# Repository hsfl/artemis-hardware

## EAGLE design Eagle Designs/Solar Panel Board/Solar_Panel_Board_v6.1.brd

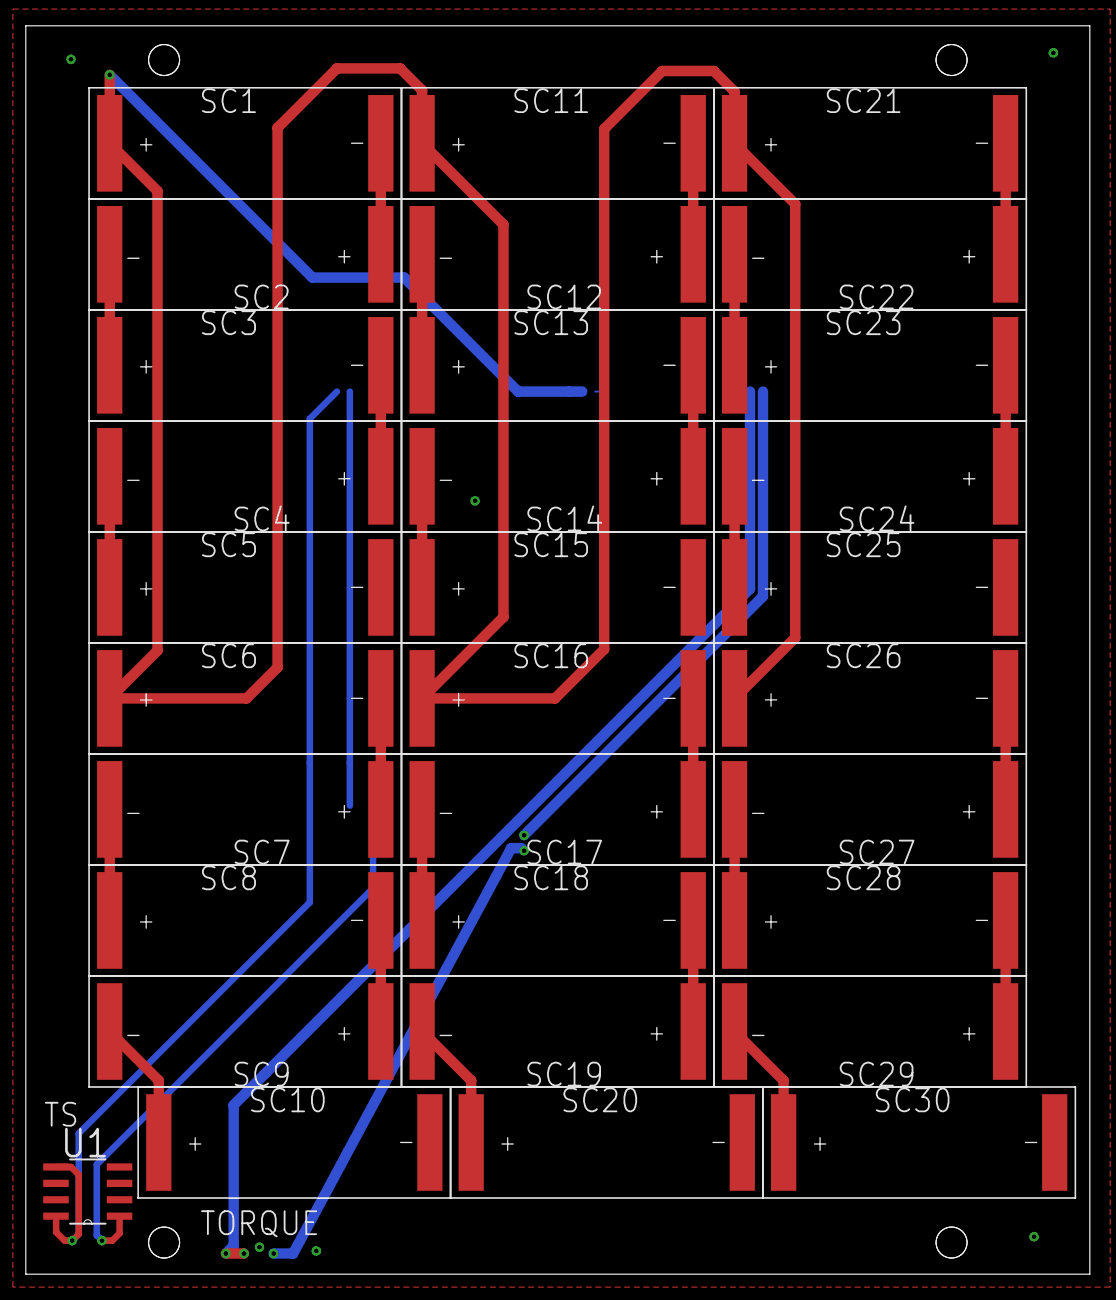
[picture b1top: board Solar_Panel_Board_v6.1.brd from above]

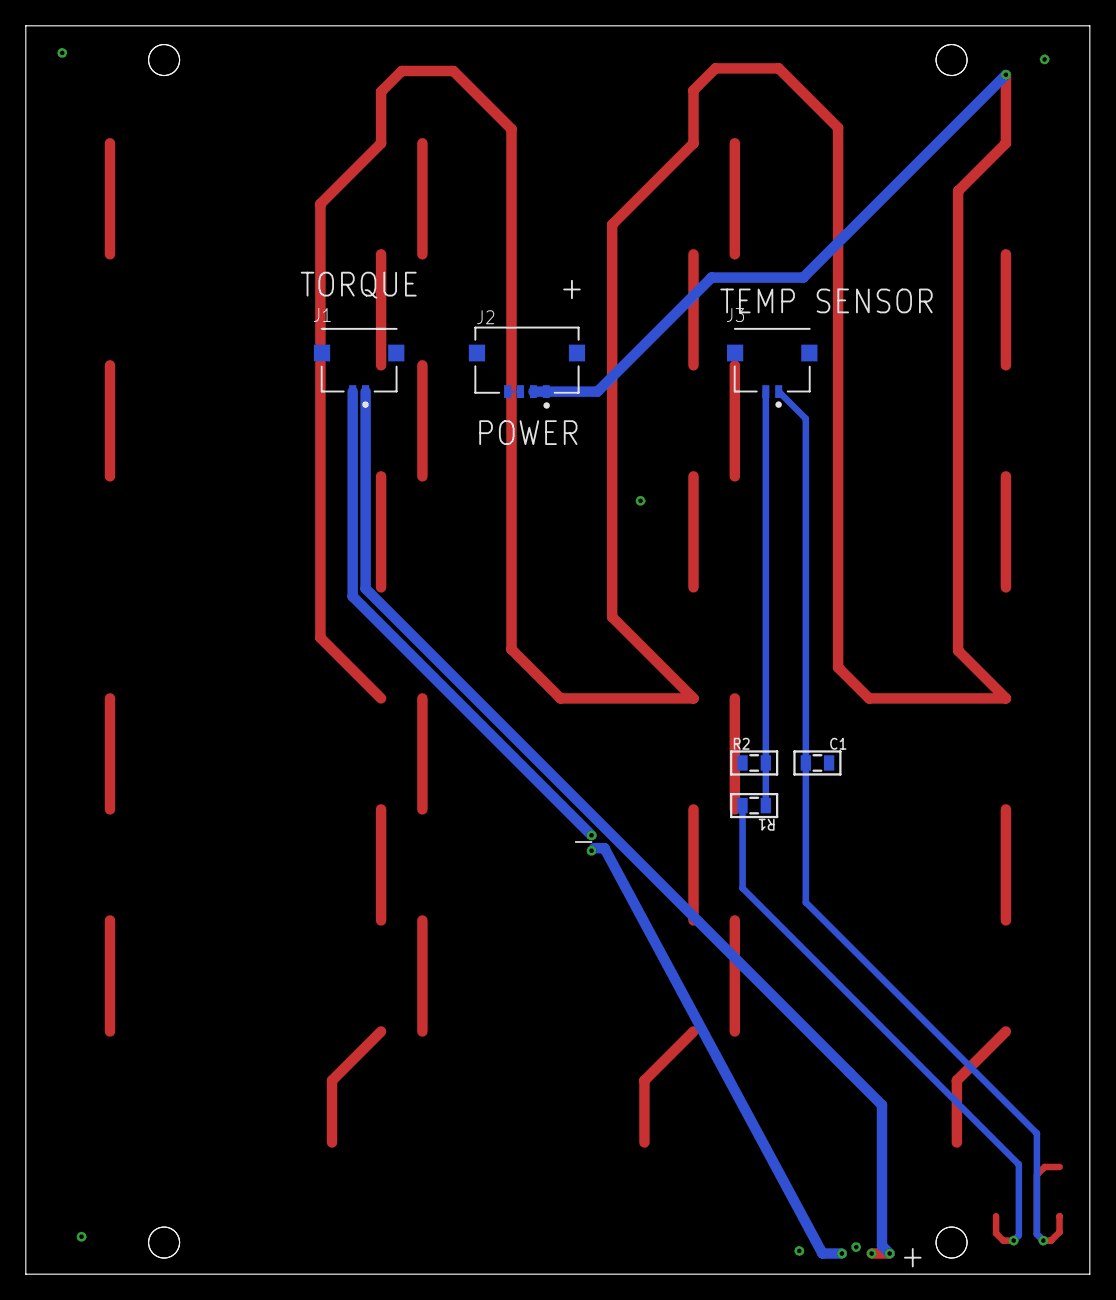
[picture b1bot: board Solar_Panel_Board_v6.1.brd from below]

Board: 4 copper layers, 82.4 x 96.7 mm, 37 parts (6 on the bottom side), 30 nets.

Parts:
C1: 0.1uF; 0805
J1, J3: MOLEX_503763-0291MOLEX_503763-0291_0_0; MOLEX_503763-0291_0
J2: MOLEX_503763-0491MOLEX_503763-0491_0_0; MOLEX_503763-0491_0
R1: 45.3k; 0805
R2: 10k; 0805
SC1, SC2, SC3, SC4, SC5, SC6, SC7, SC8, SC9, SC10, SC11, SC12, SC13, SC14, SC15, SC16, SC17, SC18, SC19, SC20, SC21, SC22, SC23, SC24, SC25, SC26, SC27, SC28, SC29, SC30: KXOB25-05X3F
U1: TMP36GSZ; SOIC127P600X175-8N

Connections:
GND: C1.2, J1.3, J1.4, J2.3, J2.4, J2.5, J2.6, J3.3, J3.4, R2.1, SC5.-, SC10.-, SC15.-, SC20.-, SC25.-, SC30.-, U1.4
unnamed: J1.1, J1.2
unnamed: SC7.-, SC8.+
unnamed: SC4.-, SC5.+
unnamed: SC3.-, SC4.+
unnamed: SC2.-, SC3.+
unnamed: SC1.-, SC2.+
unnamed: SC8.-, SC9.+
unnamed: SC16.-, SC17.+
unnamed: SC14.-, SC15.+
unnamed: SC13.-, SC14.+
unnamed: SC9.-, SC10.+
unnamed: R1.2, U1.1
unnamed: SC11.-, SC12.+
unnamed: SC23.-, SC24.+
unnamed: SC22.-, SC23.+
unnamed: SC21.-, SC22.+
unnamed: SC6.-, SC7.+
unnamed: SC17.-, SC18.+
unnamed: SC19.-, SC20.+
unnamed: SC12.-, SC13.+
unnamed: SC28.-, SC29.+
unnamed: SC29.-, SC30.+
unnamed: SC26.-, SC27.+
unnamed: SC24.-, SC25.+
unnamed: SC18.-, SC19.+
unnamed: SC27.-, SC28.+
VCC: J2.1, J2.2, SC1.+, SC6.+, SC11.+, SC16.+, SC21.+, SC26.+
VOUT: J3.2, R1.1, R2.2
VS+: C1.1, J3.1, U1.5, U1.8

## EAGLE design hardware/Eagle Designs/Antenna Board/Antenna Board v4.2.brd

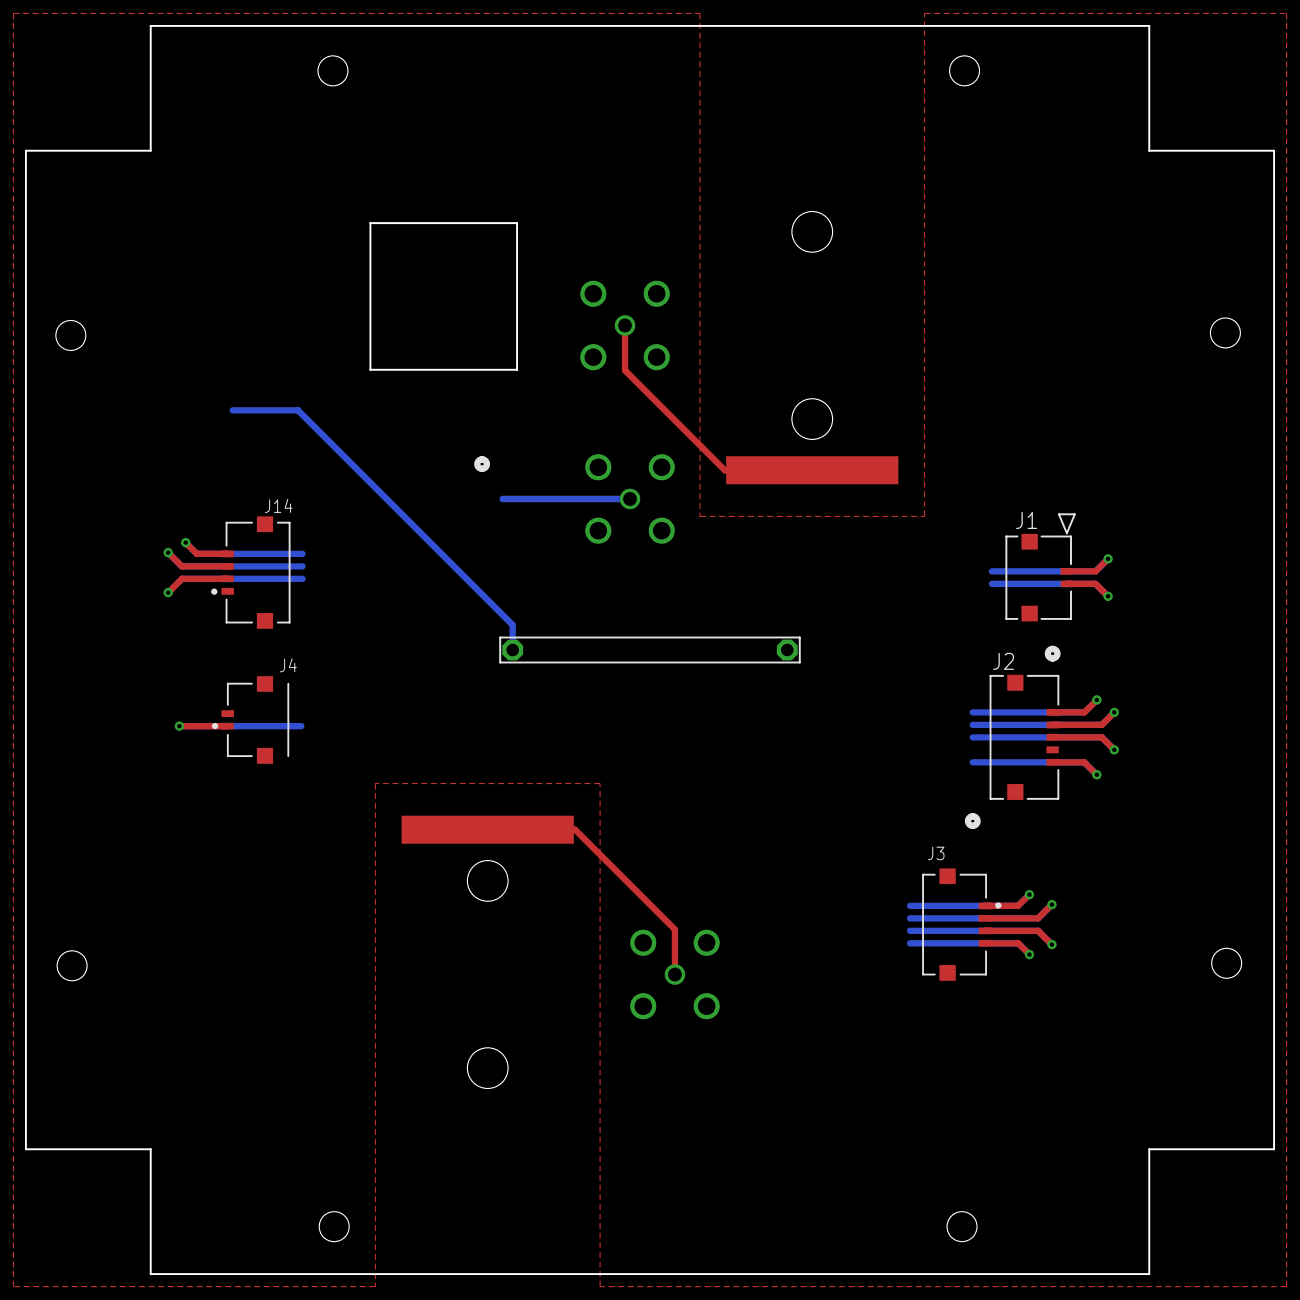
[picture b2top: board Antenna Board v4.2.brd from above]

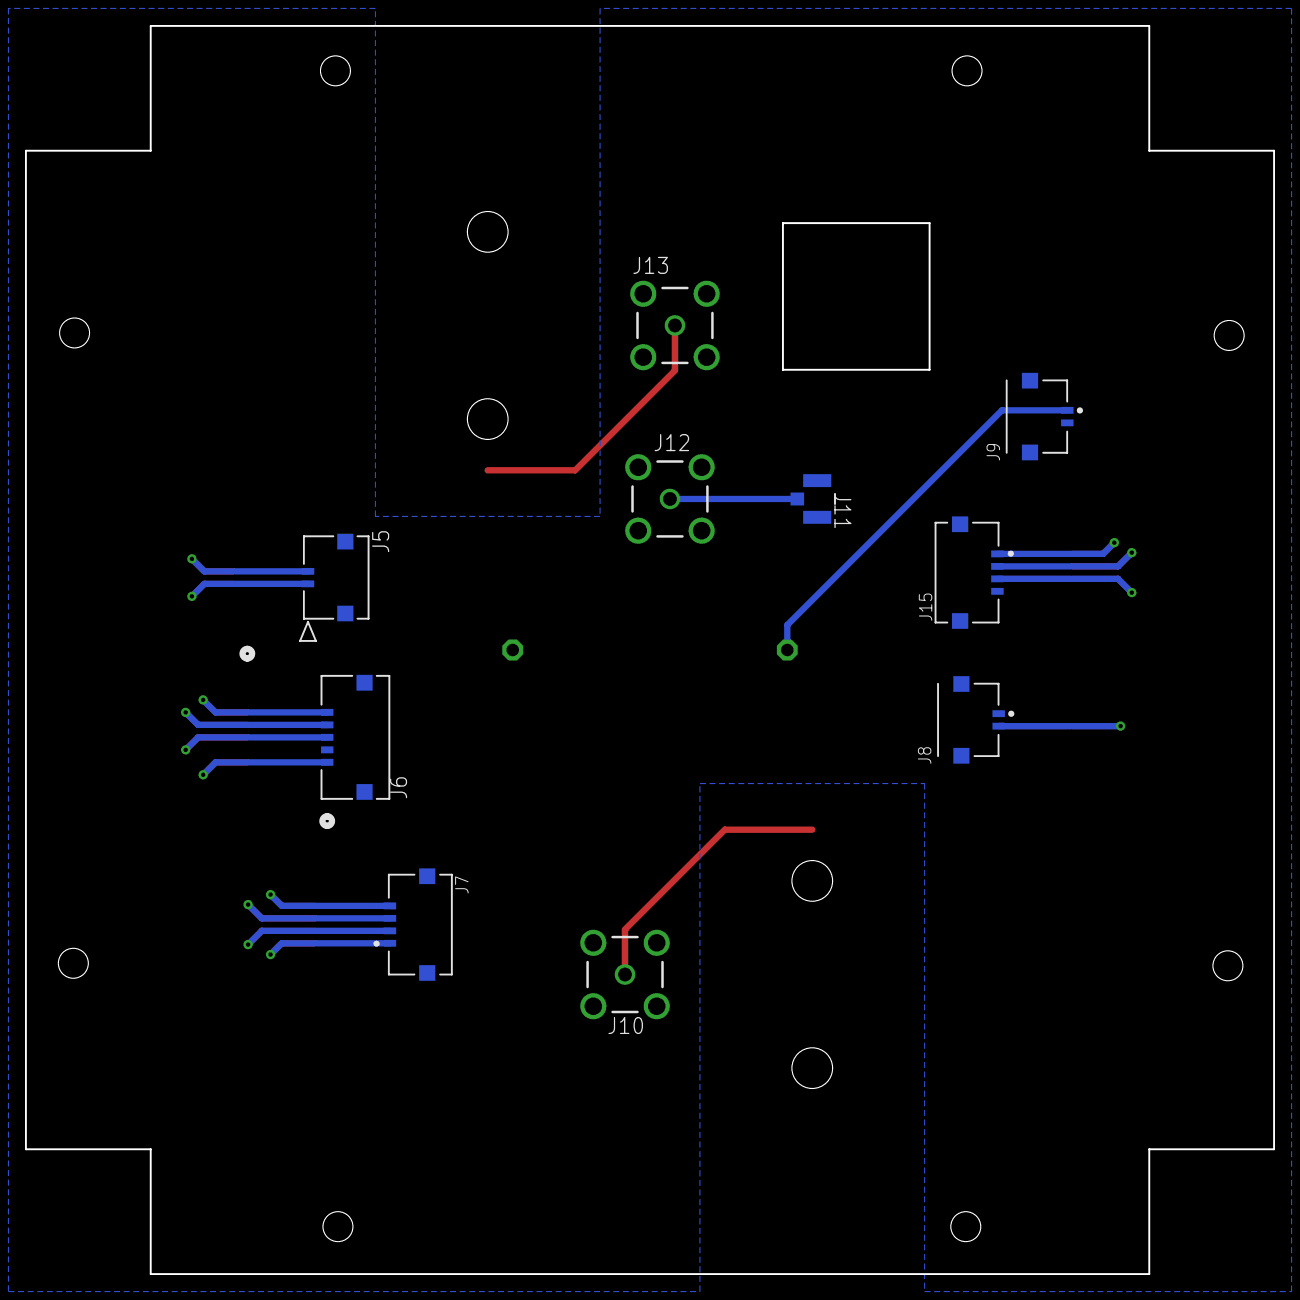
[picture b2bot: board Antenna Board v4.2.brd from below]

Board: 2 copper layers, 100.0 x 100.0 mm, 18 parts (10 on the bottom side), 19 nets.

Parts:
J1, J5: 5037630291; CON_5037630291
J2, J6: 503763-0591; CONN_5037630591_MOL
J3, J7, J14, J15: MOLEX_503763-0491MOLEX_503763-0491_0_0; MOLEX_503763-0491_0
J4, J8, J9: MOLEX_503763-0291MOLEX_503763-0291_0_0; MOLEX_503763-0291_0
J10, J12, J13: MCX-J-P-X-ST-TH1; SAMTEC_MCX-J-P-X-ST-TH1
J11: U.FL-R-SMT-1(01); CONN_-SMT-1(01)
U$1, U$2: ANTENNA_PAD+HOLES
U$3: BURNWIRE

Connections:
5V: J14.2, J15.3
ANTENNA1: J10.1, U$1.1
ANTENNA2: J13.1, U$2.1
D+: J14.3, J15.2
D-: J14.4, J15.1
GND: J1.3, J1.4, J2.4, J2.6, J2.7, J3.5, J3.6, J4.2, J4.3, J4.4, J5.3, J5.4, J6.2, J6.6, J6.7, J7.5, J7.6, J8.1, J8.3, J8.4, J9.2, J9.3, J9.4, J10.S1, J10.S2, J10.S3, J10.S4, J11.1, J11.2, J12.S1, J12.S2, J12.S3, J12.S4, J13.S1, J13.S2, J13.S3, J13.S4, J14.1, J14.5, J14.6, J15.4, J15.5, J15.6, U$3.2
ORION-SPACE: J11.3, J12.1
RBF1: J1.1, J5.2
RBF2: J1.2, J5.1
RESET: J2.1, J6.5
RX+: J3.1, J7.4
RX-: J3.2, J7.3
TCK: J2.2, J6.4
TMS: J2.3, J6.3
TX+: J3.3, J7.2
TX-: J3.4, J7.1
VCC_BATT: J4.1, J8.2
VCC_BURN: J9.1, U$3.1
VRTREF: J2.5, J6.1

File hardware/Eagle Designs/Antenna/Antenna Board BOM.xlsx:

Part | Value | Device | Package | Description
J1, J5 | 503763-0591 | 503763-0591 | CONN_5037630591_MOL
J2, J3, J6, J7 | 503763-0491 | MOLEX_503763-0491MOLEX_503763-0491_0_0 | MOLEX_503763-0491_0 | Wire-To-Board Connector, Pico-Lock 503763 Series, Surface Mount, Header, 4 Cont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
J4, J8, J9 | 503763-0291 | MOLEX_503763-0291MOLEX_503763-0291_0_0 | MOLEX_503763-0291_0 | 2 Positions Header Connector 0.039 (1.00mm) Surface Mount, Right Angle Gold"
J10 | U.FL-R-SMT-1(01) | U.FL-R-SMT-1(01) | CONN_-SMT-1(01)
U$2 | ANTENNA_PAD | ANTENNA_PAD | ANTENNA_PAD
U$3 | BURNWIRE | BURNWIRE | BURNWIRE

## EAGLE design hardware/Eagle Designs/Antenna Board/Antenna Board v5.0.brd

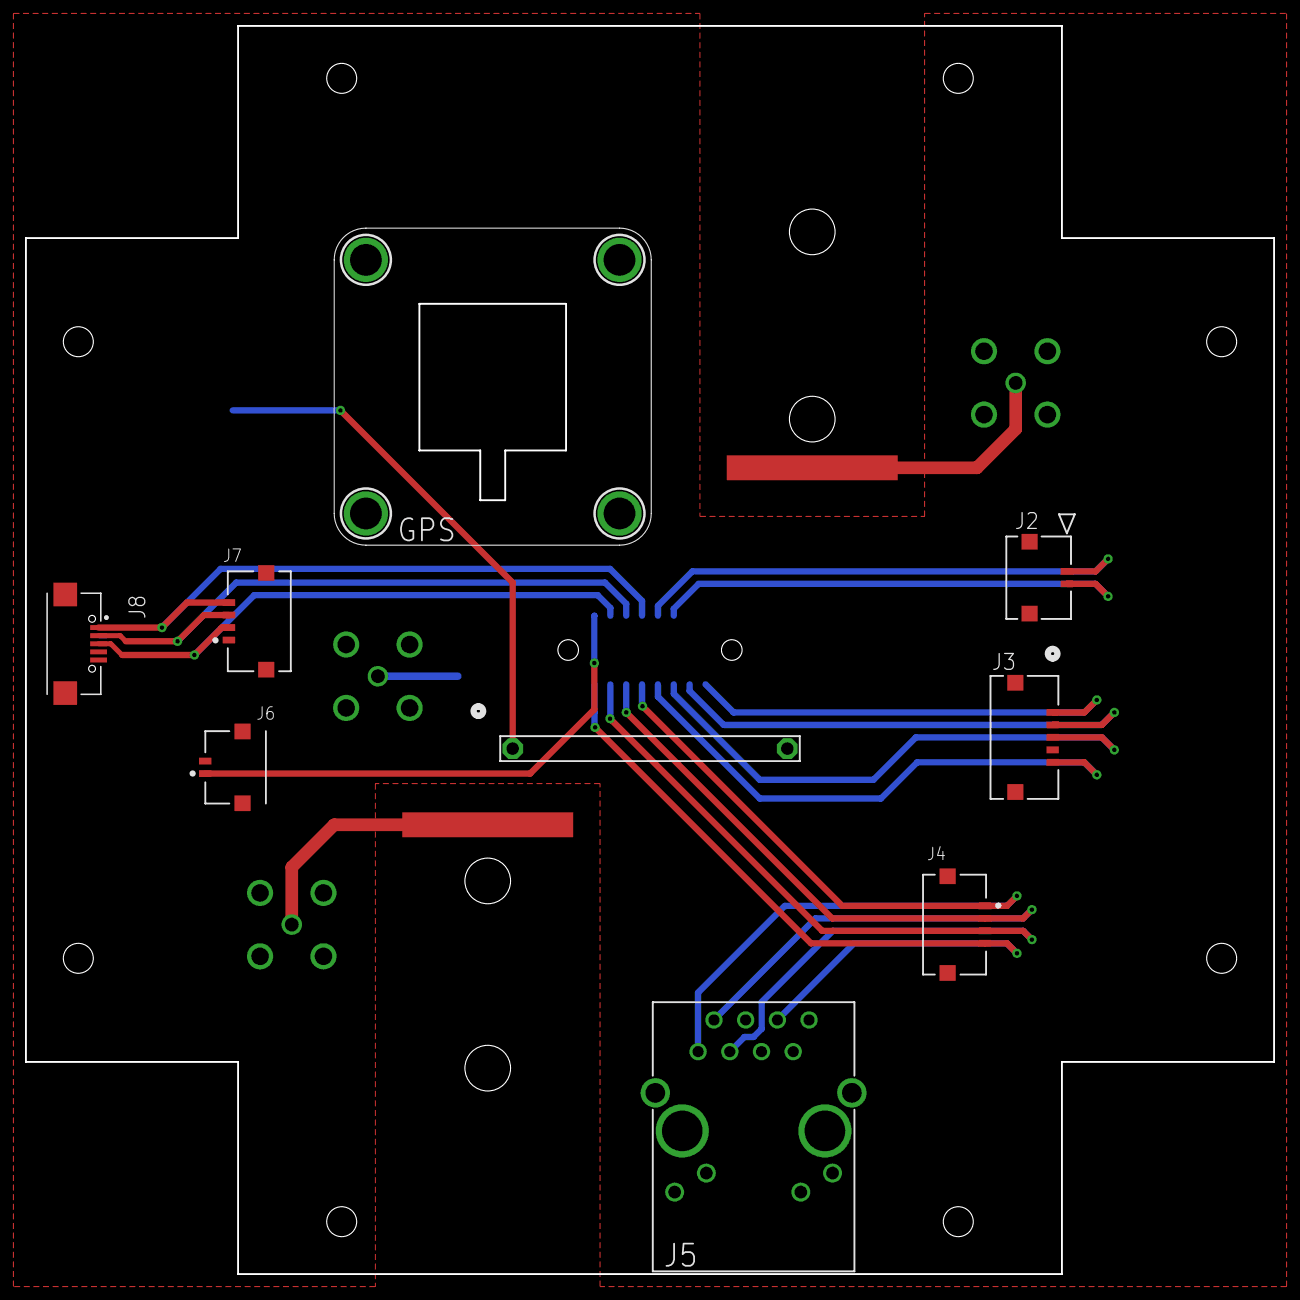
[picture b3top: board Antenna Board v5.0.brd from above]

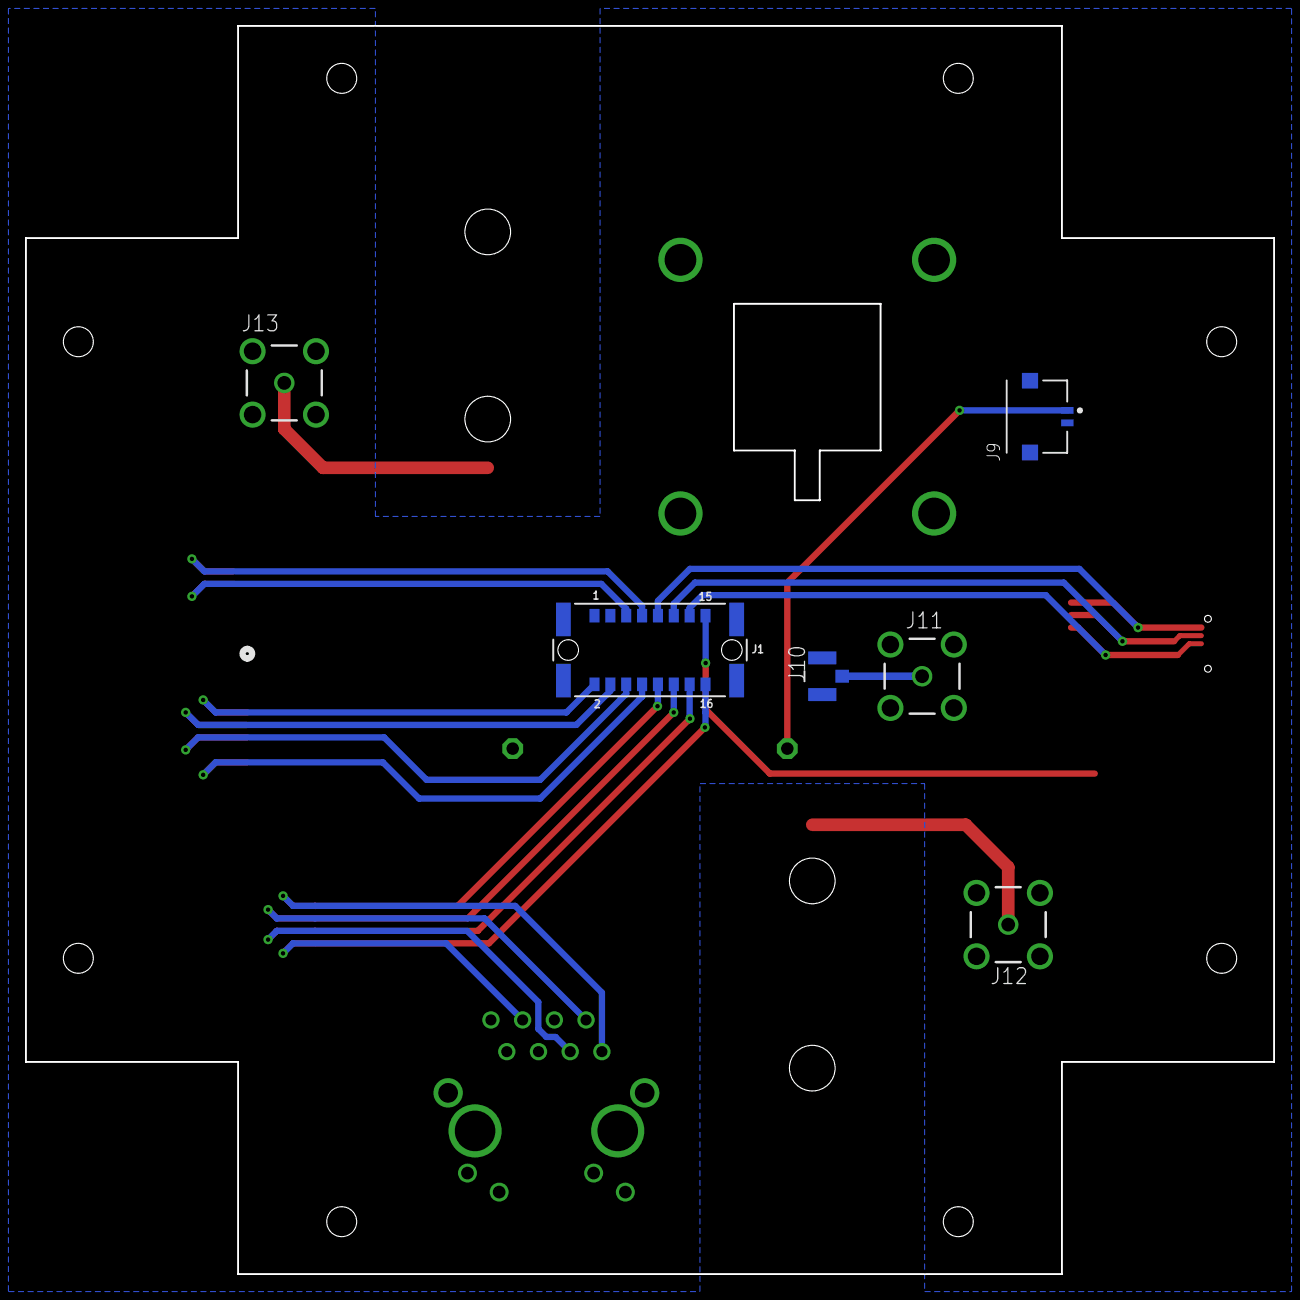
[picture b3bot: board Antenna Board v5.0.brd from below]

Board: 2 copper layers, 100.0 x 100.0 mm, 17 parts (6 on the bottom side), 19 nets.

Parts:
GPS: PA1010D
J1: M55-6001642R; CONN_M55-6001642R_HRW
J2: 5037630291; CON_5037630291
J3: 503763-0591; CONN_5037630591_MOL
J4, J7: MOLEX_503763-0491MOLEX_503763-0491_0_0; MOLEX_503763-0491_0
J5: ARJM11C7-104-AB-EW2; CONN_EW_ABR
J6, J9: MOLEX_503763-0291MOLEX_503763-0291_0_0; MOLEX_503763-0291_0
J8: UJ2-MIBH-G-SMT-TR; CUI_UJ2-MIBH-G-SMT-TR
J10: U.FL-R-SMT-1(01); CONN_-SMT-1(01)
J11, J12, J13: MCX-J-P-X-ST-TH1; SAMTEC_MCX-J-P-X-ST-TH1
U$1, U$2: ANTENNA_PAD
U$3: BURNWIRE

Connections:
5V: J1.9, J7.4, J8.1
ANTENNA1: J12.1, U$2.1
ANTENNA2: J13.1, U$1.1
D+: J1.13, J7.2, J8.3
D-: J1.11, J7.3, J8.2
GND: J1.1, J1.3, J1.19, J1.20, J1.21, J1.22, J2.3, J2.4, J3.4, J3.6, J3.7, J4.5, J4.6, J6.2, J6.3, J6.4, J7.1, J7.5, J7.6, J8.5, J8.S1, J8.S2, J9.2, J9.3, J9.4, J10.1, J10.2, J11.S1, J11.S2, J11.S3, J11.S4, J12.S1, J12.S2, J12.S3, J12.S4, J13.S1, J13.S2, J13.S3, J13.S4, U$3.2
ORION-SPACE: J10.3, J11.1
RBF1: J1.7, J2.1
RBF2: J1.5, J2.2
RESET: J1.2, J3.1
RX+: J1.14, J4.3, J5.3
RX-: J1.16, J4.4, J5.6
TCK: J1.4, J3.2
TMS: J1.6, J3.3
TX+: J1.10, J4.1, J5.1
TX-: J1.12, J4.2, J5.2
VCC_BATT: J1.15, J6.1
VCC_BURN: J9.1, U$3.1
VRTREF: J1.8, J3.5

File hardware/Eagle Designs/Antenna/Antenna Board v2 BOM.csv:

"Part";"Value";"Device";"Package";"Description";"AUTOMOTIVE";"BUILT_BY";"CENTROID_NOT_SPECIFIED";"CONN_GENDER";"CONN_ORIENTATION";"CONTACT_MATERIAL";"COPYRIGHT";"CURRENT_RATING";"DATASHEET";"DEVICE_CLASS_L1";"DEVICE_CLASS_L2";"DEVICE_CLASS_L3";"DIGIKEY_DESCRIPTION";"DIGIKEY_PART_NUMBER";"FOOTPRINT_URL";"FOOTPRINT_VARIANT_NAME_0";"HEIGHT";"LEAD_FREE";"MANUFACTURER_PART_NUMBER";"MF";"MFG_PACKAGE_IDENT";"MFG_PACKAGE_IDENT_DATE";"MFG_PACKAGE_IDENT_REV";"MOUSER_PART_NUMBER";"MPN";"NUMBER_OF_CONTACTS";"NUMBER_OF_ROWS";"PACKAGE";"PITCH";"PREFIX";"ROHS";"SOURCELIBRARY";"TEMPERATURE_RANGE_HIGH";"TEMPERATURE_RANGE_LOW";"VENDOR";"VERIFICATION_VERSION";"VOLTAGE_RATING";
"J1";"503763-0591";"503763-0591";"CONN_5037630591_MOL";"";"";"EMA_Cory";"";"";"";"";"Copyright (C) 2018 Accelerated Designs. All rights reserved";"";"https://www.molex.com/pdm_docs/sd/5037630591_sd.pdf";"";"";"";"";"";"";"";"";"";"503763-0591";"";"";"";"";"";"";"";"";"";"";"";"";"Add_to_database_2020-12-14";"";"";"Molex Connector Corporation";"";"";
"J2";"MOLEX_503763-0491MOLEX_503763-0491_0_0";"MOLEX_503763-0491MOLEX_503763-0491_0_0";"MOLEX_503763-0491_0";"Wire-To-Board Connector, Pico-Lock 503763 Series, Surface Mount, Header, 4 Contacts, 1 mm";"No";"";"No";"Male";"Right Angle";"Gold,Nickel";"";"1.5A";"https://www.molex.com/webdocs/datasheets/pdf/en-us/503763049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";"Connectors";"Headers and Wire Housings";"unset";"CONN HEADER 1MM R/A 4CKT";"WM10655CT-ND";"https://www.molex.com/pdm_docs/sd/5037630491_sd.pdf";"Recommended_Land_Pattern";"1.7mm";"Yes";"";"Molex";"503763-0491";"0";"0";"538-503763-0491";"503763-0491";"4";"1";"HDR4";"1mm";"J";"Yes";"";"+105°C";"-40°C";"";"0.0.0.1";"150V";
"J3";"MOLEX_503763-0491MOLEX_503763-0491_0_0";"MOLEX_503763-0491MOLEX_503763-0491_0_0";"MOLEX_503763-0491_0";"Wire-To-Board Connector, Pico-Lock 503763 Series, Surface Mount, Header, 4 Contacts, 1 mm";"No";"";"No";"Male";"Right Angle";"Gold,Nickel";"";"1.5A";"https://www.molex.com/webdocs/datasheets/pdf/en-us/503763049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";"Connectors";"Headers and Wire Housings";"unset";"CONN HEADER 1MM R/A 4CKT";"WM10655CT-ND";"https://www.molex.com/pdm_docs/sd/5037630491_sd.pdf";"Recommended_Land_Pattern";"1.7mm";"Yes";"";"Molex";"503763-0491";"0";"0";"538-503763-0491";"503763-0491";"4";"1";"HDR4";"1mm";"J";"Yes";"";"+105°C";"-40°C";"";"0.0.0.1";"150V";
"J4";"MOLEX_503763-0291MOLEX_503763-0291_0_0";"MOLEX_503763-0291MOLEX_503763-0291_0_0";"MOLEX_503763-0291_0";"2 Positions Header Connector 0.039" (1.00mm) Surface Mount, Right Angle Gold";"";"";"No";"";"";"";"";"";"http://www.molex.com/pdm_docs/sd/5037630291_sd.pdf";"";"";"";"CONN HEADER 1MM R/A 2CKT";"WM10654CT-ND";"";"";"";"yes";"";"Molex";"";"";"";"538-503763-0291";"503763-0291";"";"";"HDR02";"";"J";"yes";"";"+105°C";"-40°C";"";"";"";
"J5";"503763-0591";"503763-0591";"CONN_5037630591_MOL";"";"";"EMA_Cory";"";"";"";"";"Copyright (C) 2018 Accelerated Designs. All rights reserved";"";"https://www.molex.com/pdm_docs/sd/5037630591_sd.pdf";"";"";"";"";"";"";"";"";"";"503763-0591";"";"";"";"";"";"";"";"";"";"";"";"";"Add_to_database_2020-12-14";"";"";"Molex Connector Corporation";"";"";
"J6";"MOLEX_503763-0491MOLEX_503763-0491_0_0";"MOLEX_503763-0491MOLEX_503763-0491_0_0";"MOLEX_503763-0491_0";"Wire-To-Board Connector, Pico-Lock 503763 Series, Surface Mount, Header, 4 Contacts, 1 mm";"No";"";"No";"Male";"Right Angle";"Gold,Nickel";"";"1.5A";"https://www.molex.com/webdocs/datasheets/pdf/en-us/503763049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";"Connectors";"Headers and Wire Housings";"unset";"CONN HEADER 1MM R/A 4CKT";"WM10655CT-ND";"https://www.molex.com/pdm_docs/sd/5037630491_sd.pdf";"Recommended_Land_Pattern";"1.7mm";"Yes";"";"Molex";"503763-0491";"0";"0";"538-503763-0491";"503763-0491";"4";"1";"HDR4";"1mm";"J";"Yes";"";"+105°C";"-40°C";"";"0.0.0.1";"150V";
"J7";"MOLEX_503763-0491MOLEX_503763-0491_0_0";"MOLEX_503763-0491MOLEX_503763-0491_0_0";"MOLEX_503763-0491_0";"Wire-To-Board Connector, Pico-Lock 503763 Series, Surface Mount, Header, 4 Contacts, 1 mm";"No";"";"No";"Male";"Right Angle";"Gold,Nickel";"";"1.5A";"https://www.molex.com/webdocs/datasheets/pdf/en-us/503763049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";"Connectors";"Headers and Wire Housings";"unset";"CONN HEADER 1MM R/A 4CKT";"WM10655CT-ND";"https://www.molex.com/pdm_docs/sd/5037630491_sd.pdf";"Recommended_Land_Pattern";"1.7mm";"Yes";"";"Molex";"503763-0491";"0";"0";"538-503763-0491";"503763-0491";"4";"1";"HDR4";"1mm";"J";"Yes";"";"+105°C";"-40°C";"";"0.0.0.1";"150V";
"J8";"MOLEX_503763-0291MOLEX_503763-0291_0_0";"MOLEX_503763-0291MOLEX_503763-0291_0_0";"MOLEX_503763-0291_0";"2 Positions Header Connector 0.039" (1.00mm) Surface Mount, Right Angle Gold";"";"";"No";"";"";"";"";"";"http://www.molex.com/pdm_docs/sd/5037630291_sd.pdf";"";"";"";"CONN HEADER 1MM R/A 2CKT";"WM10654CT-ND";"";"";"";"yes";"";"Molex";"";"";"";"538-503763-0291";"503763-0291";"";"";"HDR02";"";"J";"yes";"";"+105°C";"-40°C";"";"";"";
"J9";"MOLEX_503763-0291MOLEX_503763-0291_0_0";"MOLEX_503763-0291MOLEX_503763-0291_0_0";"MOLEX_503763-0291_0";"2 Positions Header Connector 0.039" (1.00mm) Surface Mount, Right Angle Gold";"";"";"No";"";"";"";"";"";"http://www.molex.com/pdm_docs/sd/5037630291_sd.pdf";"";"";"";"CONN HEADER 1MM R/A 2CKT";"WM10654CT-ND";"";"";"";"yes";"";"Molex";"";"";"";"538-503763-0291";"503763-0291";"";"";"HDR02";"";"J";"yes";"";"+105°C";"-40°C";"";"";"";
"J10";"U.FL-R-SMT-1(01)";"U.FL-R-SMT-1(01)";"CONN_-SMT-1(01)";"";"";"EMA_Matt";"";"";"";"";"Copyright (C) 2018 Accelerated Designs. All rights reserved";"";"";"";"";"";"";"";"";"";"";"";"U.FL-R-SMT-1(01)";"";"";"";"";"";"";"";"";"";"";"";"";"Hirose_12_20_2019";"";"";"Hirose";"";"";
"J11";"U.FL-R-SMT-1(01)";"U.FL-R-SMT-1(01)";"CONN_-SMT-1(01)";"";"";"EMA_Matt";"";"";"";"";"Copyright (C) 2018 Accelerated Designs. All rights reserved";"";"";"";"";"";"";"";"";"";"";"";"U.FL-R-SMT-1(01)";"";"";"";"";"";"";"";"";"";"";"";"";"Hirose_12_20_2019";"";"";"Hirose";"";"";
"J12";"U.FL-R-SMT-1(01)";"U.FL-R-SMT-1(01)";"CONN_-SMT-1(01)";"";"";"EMA_Matt";"";"";"";"";"Copyright (C) 2018 Accelerated Designs. All rights reserved";"";"";"";"";"";"";"";"";"";"";"";"U.FL-R-SMT-1(01)";"";"";"";"";"";"";"";"";"";"";"";"";"Hirose_12_20_2019";"";"";"Hirose";"";"";
"U$2";"ANTENNA_PAD";"ANTENNA_PAD";"ANTENNA_PAD";"";"";"";"";"";"";"";"";"";"";"";"";"";"";"";"";"";"";"";"";"";"";"";"";"";"";"";"";"";"";"";"";"";"";"";"";"";"";
"U$3";"BURNWIRE";"BURNWIRE";"BURNWIRE";"";"";"";"";"";"";"";"";"";"";"";"";"";"";"";"";"";"";"";"";"";"";"";"";"";"";"";"";"";"";"";"";"";"";"";"";"";"";

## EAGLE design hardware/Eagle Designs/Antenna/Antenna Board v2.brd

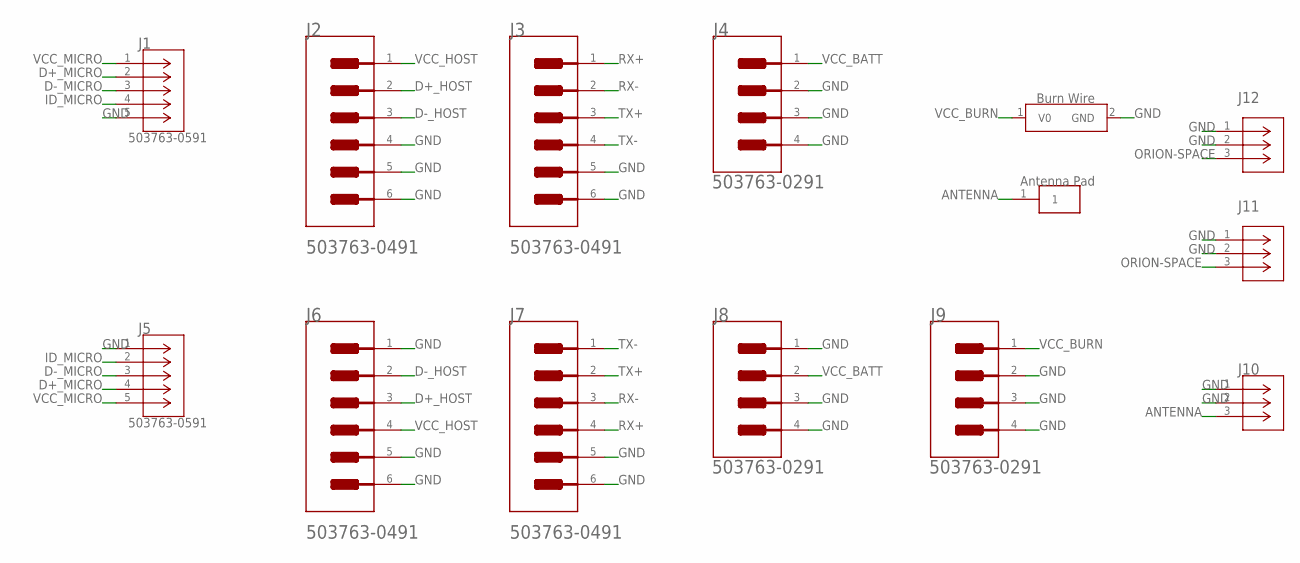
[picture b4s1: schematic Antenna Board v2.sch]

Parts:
J1, J5: 503763-0591; CONN_5037630591_MOL
J2, J3, J6, J7: MOLEX_503763-0491MOLEX_503763-0491_0_0; MOLEX_503763-0491_0
J4, J8, J9: MOLEX_503763-0291MOLEX_503763-0291_0_0; MOLEX_503763-0291_0
J10, J11, J12: U.FL-R-SMT-1(01); CONN_-SMT-1(01)
U$2: ANTENNA_PAD
U$3: BURNWIRE

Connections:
ANTENNA: J10.3, U$2.1
D+_HOST: J2.2, J6.3
D+_MICRO: J1.2, J5.4
D-_HOST: J2.3, J6.2
D-_MICRO: J1.3, J5.3
GND: J1.5, J1.6, J1.7, J2.4, J2.5 (MNT_1), J2.6 (MNT_2), J3.5 (MNT_1), J3.6 (MNT_2), J4.2, J4.3 (MNT_1), J4.4 (MNT_2), J5.1, J5.6, J5.7, J6.1, J6.5 (MNT_1), J6.6 (MNT_2), J7.5 (MNT_1), J7.6 (MNT_2), J8.1, J8.3 (MNT_1), J8.4 (MNT_2), J9.2, J9.3 (MNT_1), J9.4 (MNT_2), J10.1, J10.2, J11.1, J11.2, J12.1, J12.2, U$3.2 (GND)
ID_MICRO: J1.4, J5.2
ORION-SPACE: J11.3, J12.3
RX+: J3.1, J7.4
RX-: J3.2, J7.3
TX+: J3.3, J7.2
TX-: J3.4, J7.1
VCC_BATT: J4.1, J8.2
VCC_BURN: J9.1, U$3.1 (V0)
VCC_HOST: J2.1, J6.4
VCC_MICRO: J1.1, J5.5

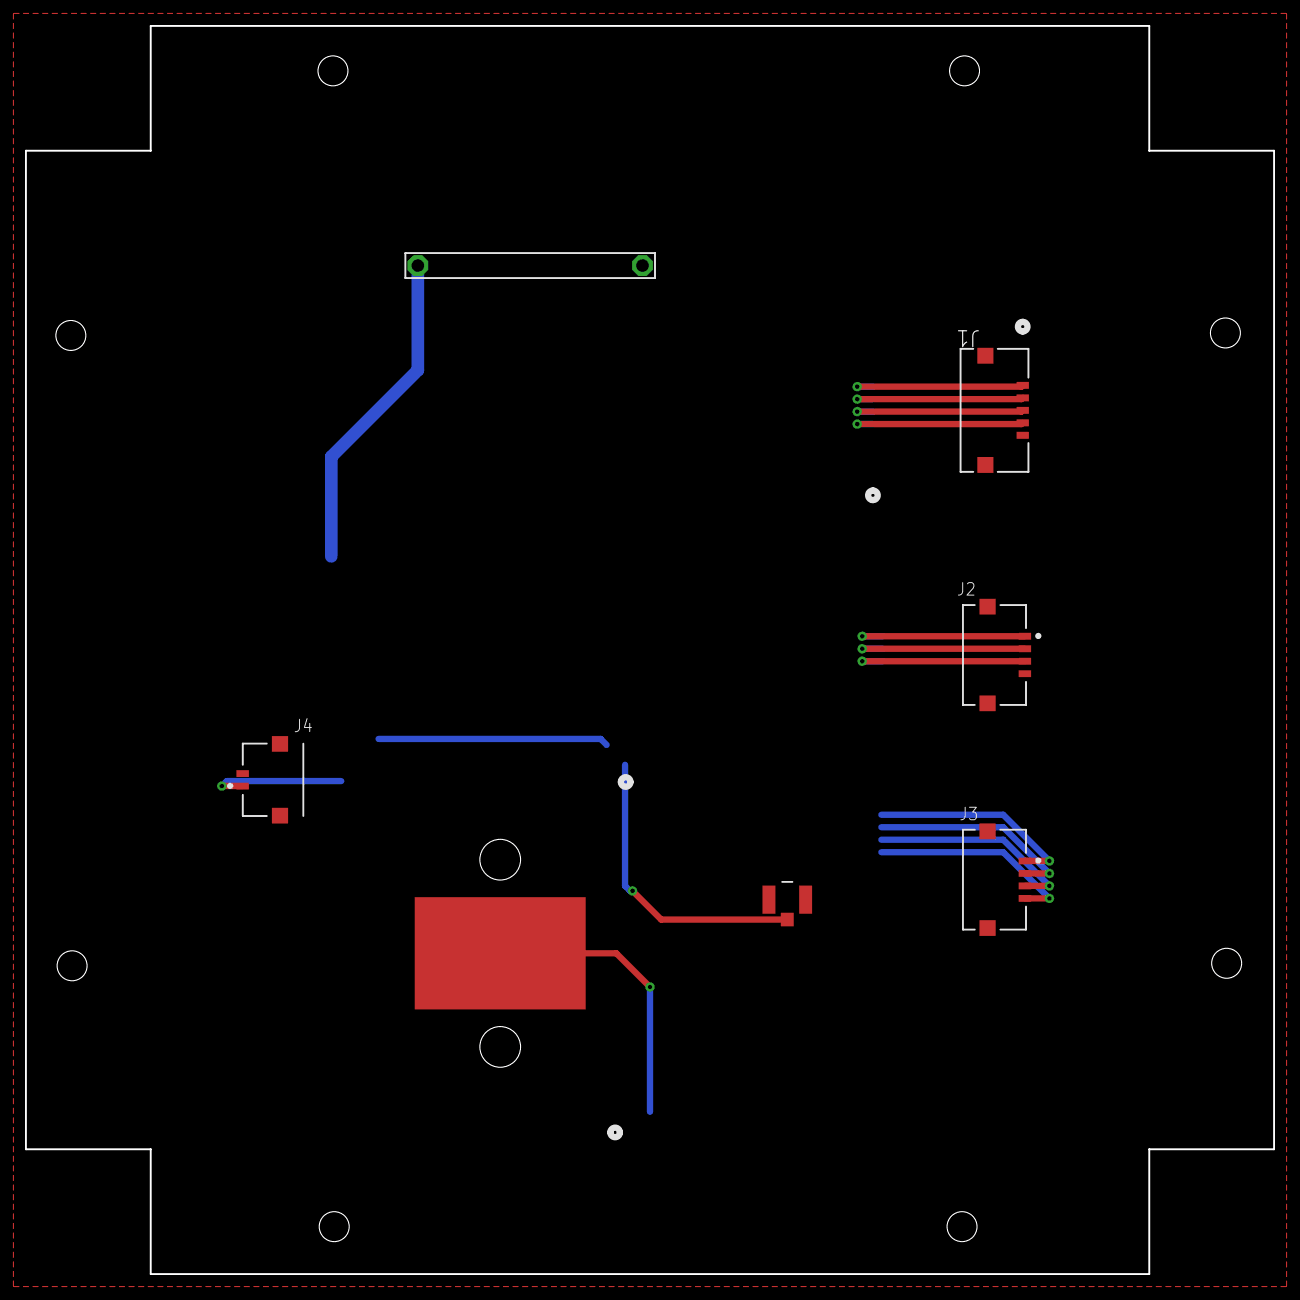
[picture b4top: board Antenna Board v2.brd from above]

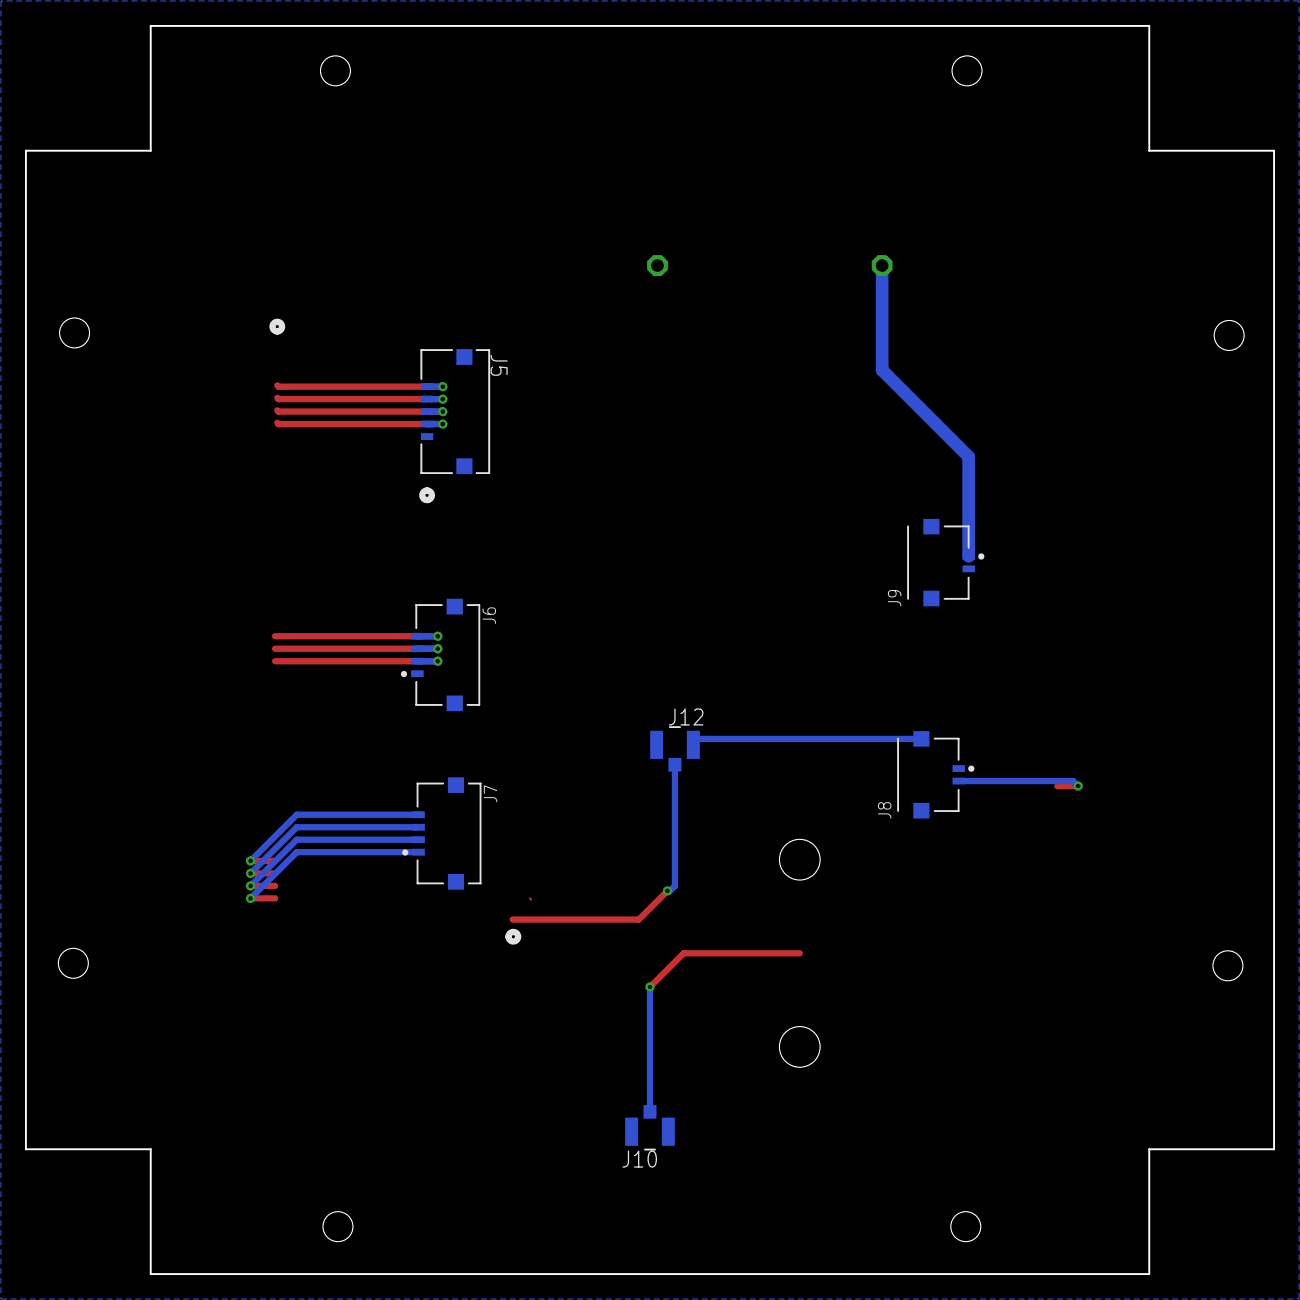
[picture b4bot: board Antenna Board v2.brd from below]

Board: 2 copper layers, 100.0 x 100.0 mm, 14 parts (7 on the bottom side), 16 nets.

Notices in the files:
parts and their libraries:
U.FL-R-SMT-1: COPYRIGHT: Copyright (C) 2018 Accelerated Designs. All rights reserved
COPYRIGHT: Copyright (C) 2021 Ultra Librarian. All rights reserved.
